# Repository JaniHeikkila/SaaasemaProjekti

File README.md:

# SaaasemaProjekti

Tarkoituksena oli tehdä sääasema joka mittaa lämpötilaa, ilmanpainetta, -kosteutta, sademäärää sekä tuulennopeutta. Projekti suunniteltiin ja rakennettiin piirilevyä myöten itse. Projekti onnistui suunnitelmien mukaisesti.

Valmis projekti

Jänniteregulaattori

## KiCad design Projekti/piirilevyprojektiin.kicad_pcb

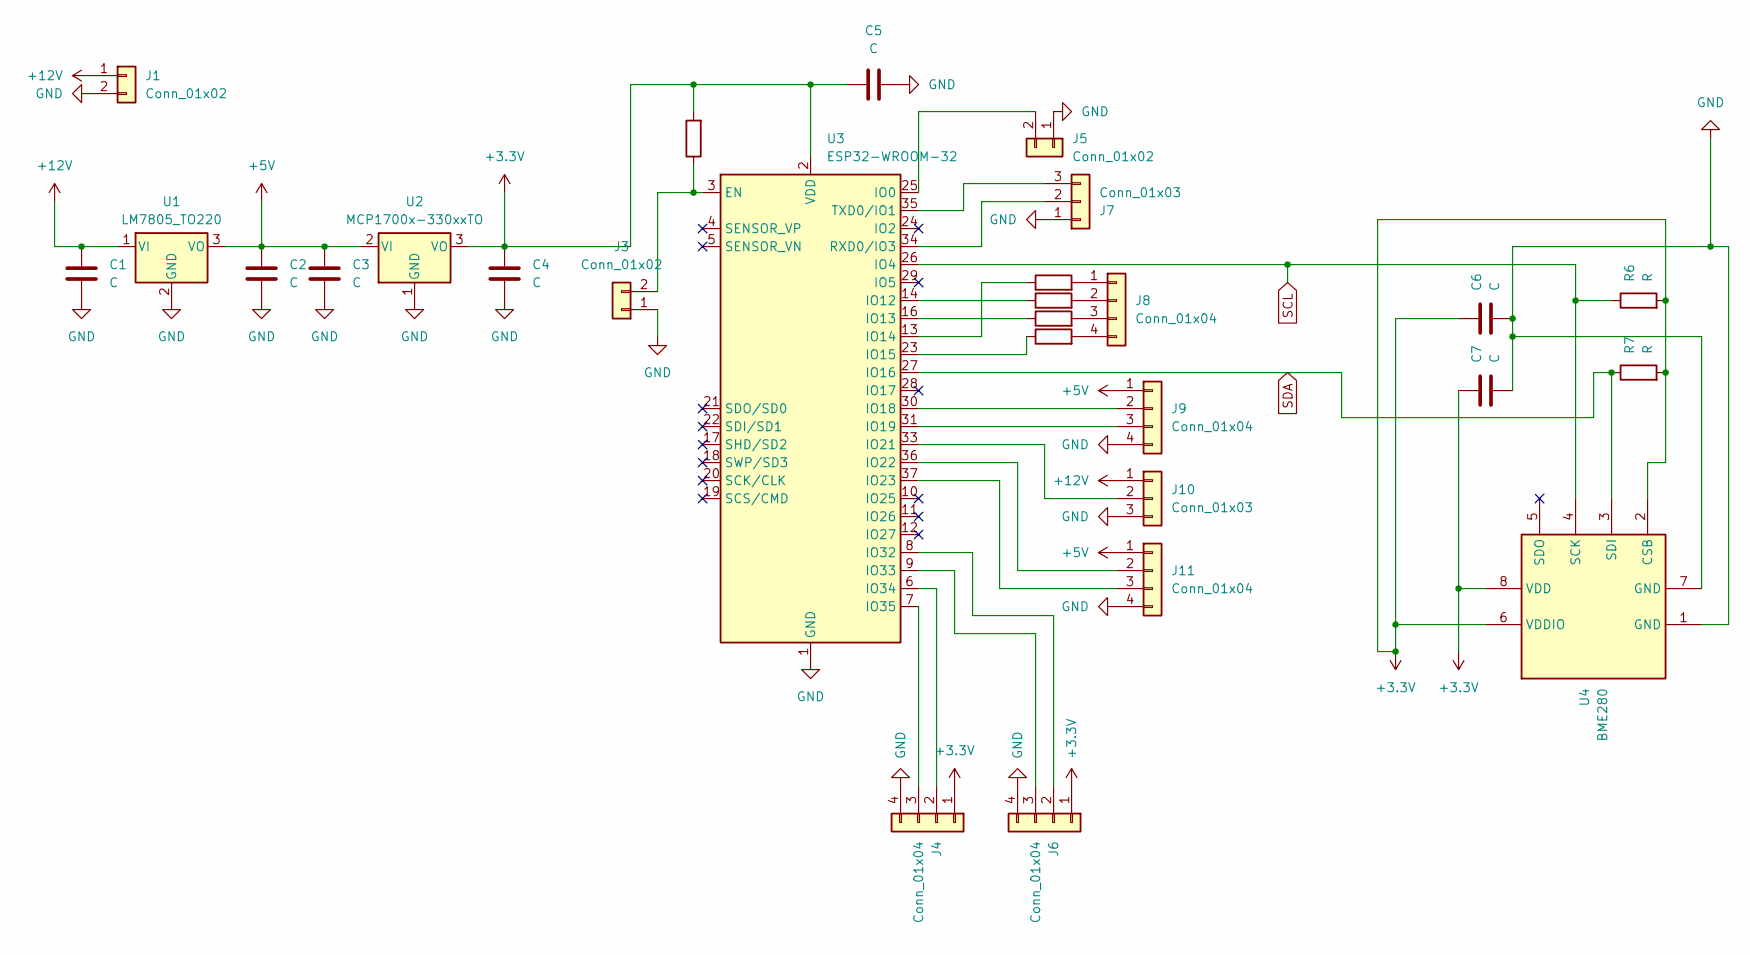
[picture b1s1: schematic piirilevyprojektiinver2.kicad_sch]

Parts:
C1, C2, C3, C4, C5, C6, C7: C; C_Radial_D6.3mm_H7.0mm_P2.50mm
J1, J3, J5: Conn_01x02; PinHeader_1x02_P2.54mm_Vertical
J4, J6, J8, J9, J11: Conn_01x04; PinHeader_1x04_P2.54mm_Vertical
J7, J10: Conn_01x03; PinHeader_1x03_P2.54mm_Vertical
R1, R2, R3, R4, R5: R; R_Axial_DIN0309_L9.0mm_D3.2mm_P12.70mm_Horizontal
R6, R7: R; R_Axial_DIN0411_L9.9mm_D3.6mm_P12.70mm_Horizontal
U1: LM7805_TO220; TO-220-3_Horizontal_TabDown
U2: MCP1700x-330xxTO; TO-92L_HandSolder
U3: ESP32-WROOM-32
U4: BME280; Bosch_LGA-8_2.5x2.5mm_P0.65mm_ClockwisePinNumbering

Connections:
+3.3V: C4.1, C5.2, C6.1, C7.1, J4.1, J6.1, R1.2, R6.2, R7.2, U2.3 (VO), U3.2 (VDD), U4.2 (CSB), U4.6 (VDDIO), U4.8 (VDD)
+5V: C2.1, C3.1, J9.1, J11.1, U1.3 (VO), U2.2 (VI)
+12V: C1.1, J1.1, J10.1, U1.1 (VI)
GND: C1.2, C2.2, C3.2, C4.2, C5.1, C6.2, C7.2, J1.2, J3.1, J4.4, J5.1, J6.4, J7.1, J9.4, J10.3, J11.4, U1.2 (GND), U2.1 (GND), U3.1 (GND), U3.15 (GND), U3.38 (GND), U3.39 (GND), U4.1 (GND), U4.7 (GND)
unnamed: J3.2, R1.1, U3.3 (EN)
unnamed: J4.2, U3.6 (IO34)
unnamed: J4.3, U3.7 (IO35)
unnamed: J5.2, U3.25 (IO0)
unnamed: J6.2, U3.8 (IO32)
unnamed: J6.3, U3.9 (IO33)
unnamed: J7.2, U3.34 (RXD0/IO3)
unnamed: J7.3, U3.35 (TXD0/IO1)
unnamed: J8.1, R2.2
unnamed: J8.2, R3.2
unnamed: J8.3, R4.2
unnamed: J8.4, R5.2
unnamed: J9.2, U3.30 (IO18)
unnamed: J9.3, U3.31 (IO19)
unnamed: J10.2, U3.33 (IO21)
unnamed: J11.2, U3.36 (IO22)
unnamed: J11.3, U3.37 (IO23)
unnamed: R3.1, U3.14 (IO12)
unnamed: R4.1, U3.16 (IO13)
unnamed: R2.1, U3.13 (IO14)
unnamed: R5.1, U3.23 (IO15)
SCL: R6.1, U3.26 (IO4), U4.4 (SCK)
SDA: R7.1, U3.27 (IO16), U4.3 (SDI)

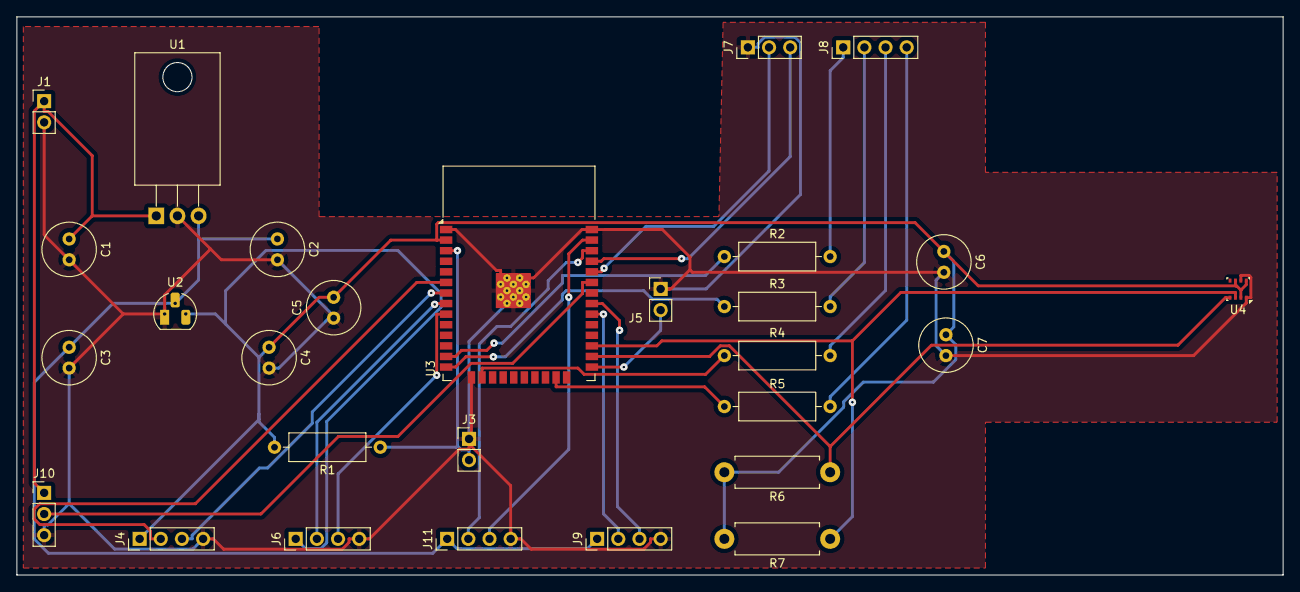
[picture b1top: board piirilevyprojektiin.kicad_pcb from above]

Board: 2 copper layers, 152.0 x 67.0 mm, 28 parts (0 on the bottom side), 27 nets.
